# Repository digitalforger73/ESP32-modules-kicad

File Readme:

# ESP32 Community Hardware Project

An open community project for learning ESP32 hardware design with KiCad.

This repository contains a complete ESP32 development board designed in KiCad, intended for makers, students, and engineers who want to learn custom PCB design and build their own ESP32-based hardware.

---

## Features

- ESP32-WROOM-32E
- USB Serial (CH340)
- 3.3V Power Regulator
- Reset / User Buttons
- A status LED / A user LED
- Programming Circuit
- Expansion Headers
- Symbols and Footprints on Components
- Component Replacement Guide

---

## Preview

### PCB

### Schematic

---

## Who is this project for?

- ESP32 beginners
- Electronics hobbyists
- PCB designers
- Students
- Engineers learning KiCad
- Makers who want to build their own ESP32 board

---

## Community Edition

This repository contains the **Community Edition**.

The goal is to provide a minimal but practical ESP32 reference design that anyone can study and build.

---

## Professional Editions

Professional versions are available separately and include additional features such as:

- Buck-Boost Power Supply
- LiPo Battery Charger
- Ultra-Low-Power Design
- Battery Powered Operation
- Additional Sensors
- Production-ready Hardware

---

## Documentation

- Component Replacement Guide
- Assembly Guide
- Hardware Documentation

---

## License

This project is licensed under the **Ippeul Community Hardware License (ICHL)**.

See the LICENSE file for details.

---

## Website

https://www.ippeul.io

---

## Support

If you find this project useful, please consider:

- ⭐ Starring this repository
- Sharing it with other makers
- Visiting https://www.ippeul.io

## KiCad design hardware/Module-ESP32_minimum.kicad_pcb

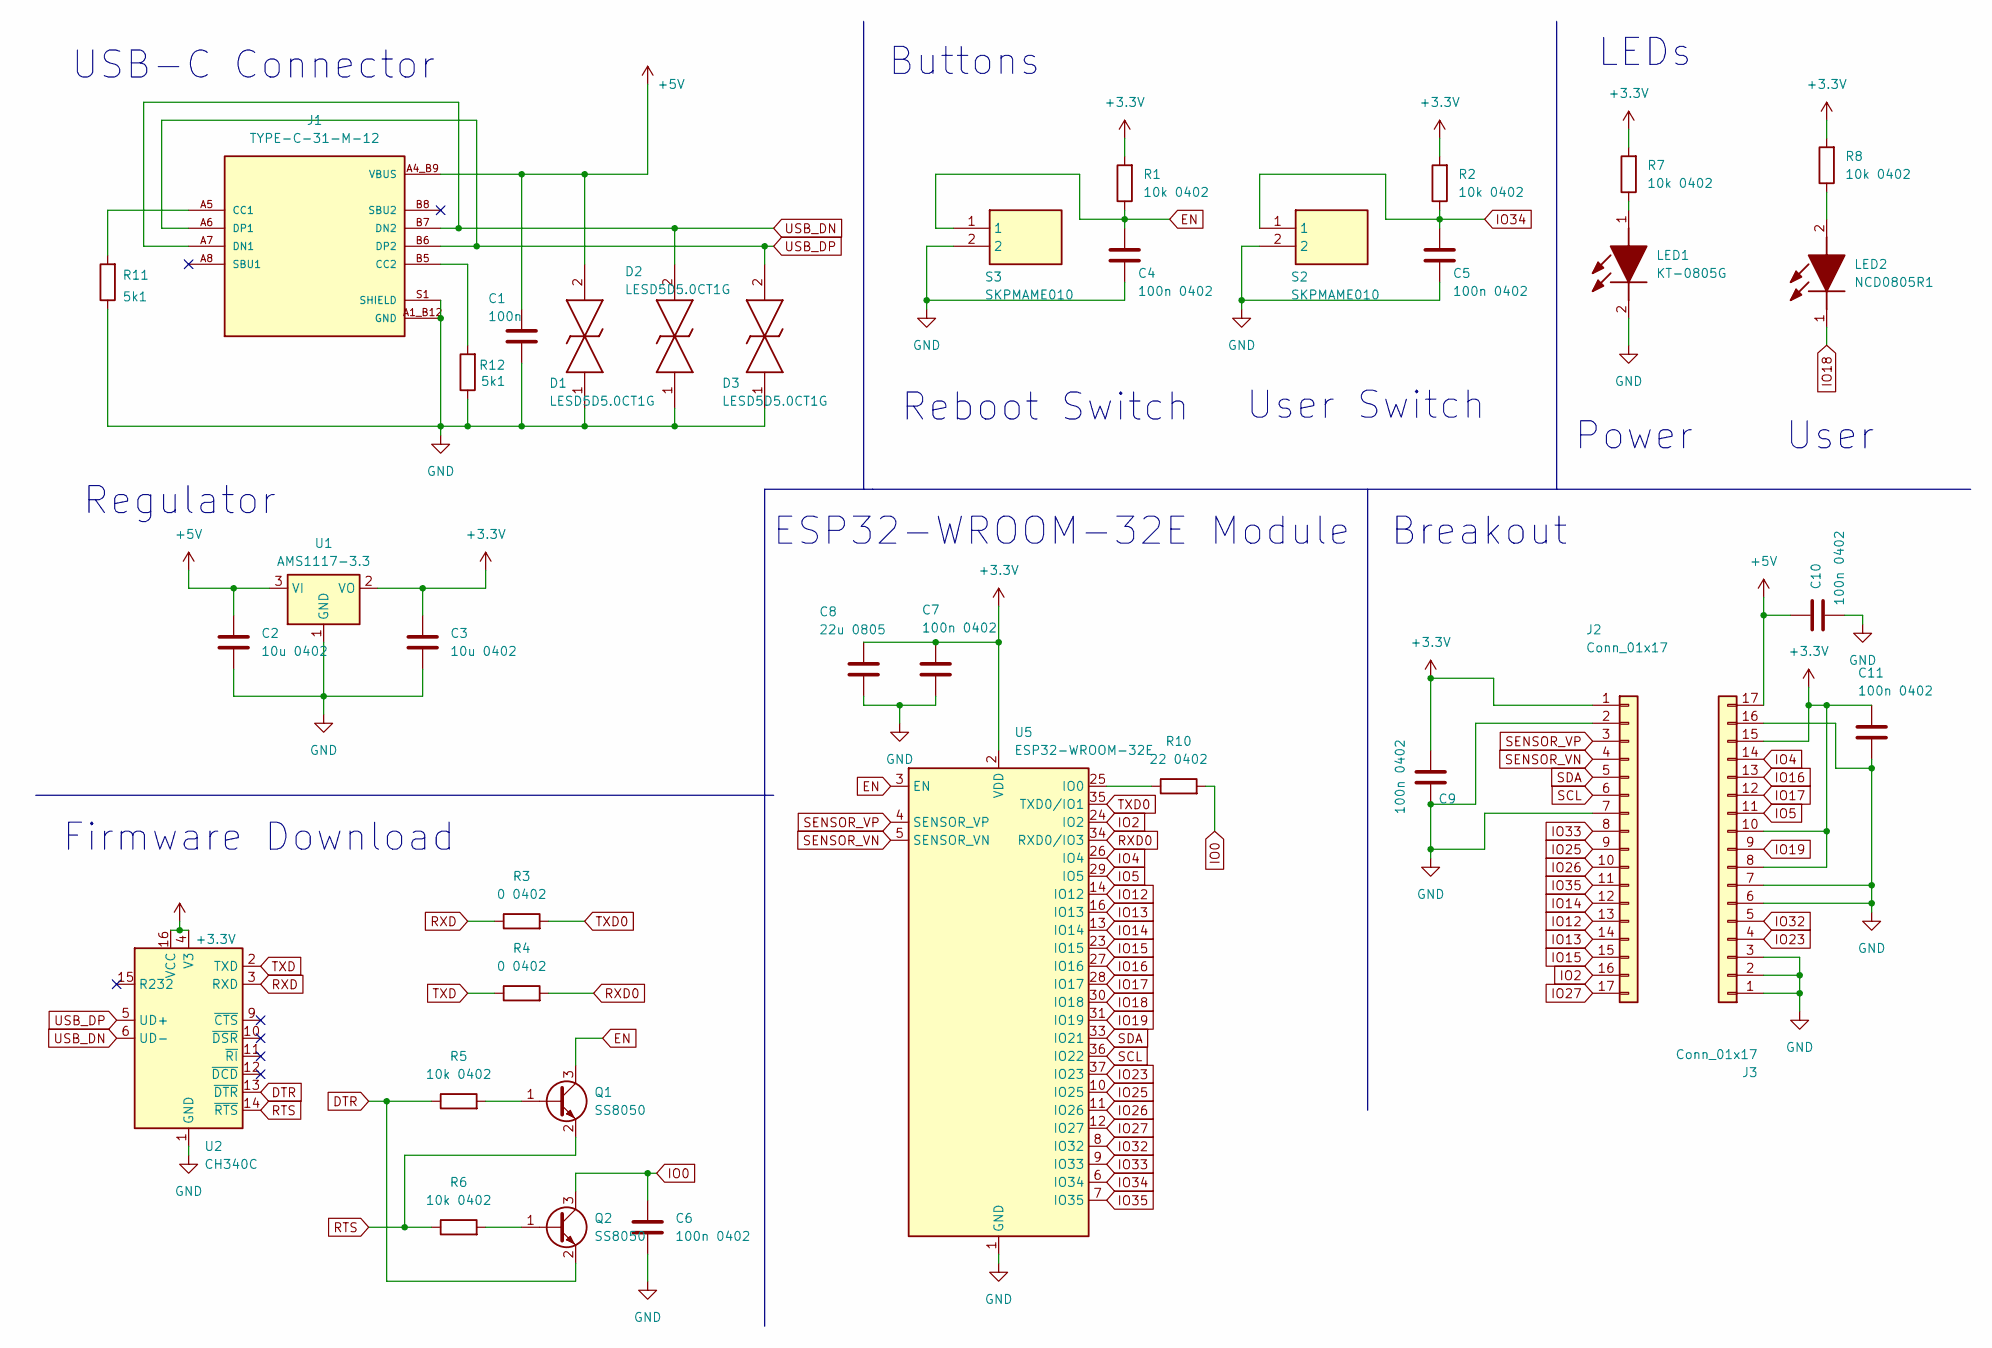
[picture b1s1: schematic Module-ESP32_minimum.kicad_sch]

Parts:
C1: 100n; C_0402_1005Metric
C2, C3: 10u 0402; C_0402_1005Metric
C4, C5, C6, C7, C9, C10, C11: 100n 0402; C_0402_1005Metric
C8: 22u 0805; C_0805_2012Metric
D1, D2, D3: LESD5D5.0CT1G; LESD5D50CT1G; Manufacturer_Part_Number LESD5D5.0CT1G
J1: TYPE-C-31-M-12; HRO_TYPE-C-31-M-12; PARTREV 2020.12.08
J2, J3: Conn_01x17; PinHeader_1x17_P1.27mm_Vertical
LED1: KT-0805G; KT0805G; Manufacturer_Part_Number KT-0805G
LED2: NCD0805R1; LEDC2012X120N; Manufacturer_Part_Number NCD0805R1
Q1, Q2: SS8050; SOT-23
R1, R2, R5, R6, R7, R8: 10k 0402; R_0402_1005Metric
R3, R4: 0 0402; R_0402_1005Metric
R10: 22 0402; R_0402_1005Metric
R11, R12: 5k1; R_0402_1005Metric
S2, S3: SKPMAME010; Manufacturer_Part_Number SKPMAME010; Mouser Part Number 688-SKPMAM
U1: AMS1117-3.3; SOT-223-3_TabPin2
U2: CH340C; STC_SOP-16_3.9x9.9mm_P1.27mm
U5: ESP32-WROOM-32E; ESP32-WROOM-32D

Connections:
+3.3V: C3.1, C7.1, C8.1, C9.1, C11.1, J2.1, J3.8, J3.10, J3.15, R1.2, R2.2, R7.2, R8.2, U1.2 (VO), U2.4 (V3), U2.16 (VCC), U5.2 (VDD)
+5V: C1.1, C2.1, C10.1, D1.2, J1.A4_B9 (VBUS), J1.B4_A9 (VBUS), J3.17, U1.3 (VI)
DTR: Q2.2 (E), R5.1, U2.13 (~DTR)
EN: C4.1, Q1.3 (C), R1.1, S3.1, U5.3 (EN)
GND: C1.2, C2.2, C3.2, C4.2, C5.2, C6.2, C7.2, C8.2, C9.2, C10.2, C11.2, D1.1, D2.1, D3.1, J1.A1_B12 (GND), J1.B1_A12 (GND), J1.S1 (SHIELD), J1.S2 (SHIELD), J1.S3 (SHIELD), J1.S4 (SHIELD), J2.2, J2.7, J3.1, J3.2, J3.3, J3.6, J3.7, J3.16, LED1.2 (K), R11.1, R12.1, S2.2, S3.2, U1.1 (GND), U2.1 (GND), U5.1 (GND), U5.15 (GND), U5.38 (GND), U5.39 (GND)
IO0: C6.1, Q2.3 (C), R10.2
IO2: J2.16, U5.24 (IO2)
IO4: J3.14, U5.26 (IO4)
IO5: J3.11, U5.29 (IO5)
IO12: J2.13, U5.14 (IO12)
IO13: J2.14, U5.16 (IO13)
IO14: J2.12, U5.13 (IO14)
IO15: J2.15, U5.23 (IO15)
IO16: J3.13, U5.27 (IO16)
IO17: J3.12, U5.28 (IO17)
IO18: LED2.1 (K), U5.30 (IO18)
IO19: J3.9, U5.31 (IO19)
IO23: J3.4, U5.37 (IO23)
IO25: J2.9, U5.10 (IO25)
IO26: J2.10, U5.11 (IO26)
IO27: J2.17, U5.12 (IO27)
IO32: J3.5, U5.8 (IO32)
IO33: J2.8, U5.9 (IO33)
IO34: C5.1, R2.1, S2.1, U5.6 (IO34)
IO35: J2.11, U5.7 (IO35)
unnamed: J1.A5 (CC1), R11.2
unnamed: J1.B5 (CC2), R12.2
unnamed: LED1.1 (A), R7.1
unnamed: LED2.2 (A), R8.1
unnamed: Q1.1 (B), R5.2
unnamed: Q2.1 (B), R6.2
unnamed: R10.1, U5.25 (IO0)
RTS: Q1.2 (E), R6.1, U2.14 (~RTS)
RXD: R3.1, U2.3 (RXD)
RXD0: R4.2, U5.34 (RXD0/IO3)
SCL: J2.6, U5.36 (IO22)
SDA: J2.5, U5.33 (IO21)
SENSOR_VN: J2.4, U5.5 (SENSOR_VN)
SENSOR_VP: J2.3, U5.4 (SENSOR_VP)
TXD: R4.1, U2.2 (TXD)
TXD0: R3.2, U5.35 (TXD0/IO1)
USB_DN: D2.2, J1.A7 (DN1), J1.B7 (DN2), U2.6 (UD-)
USB_DP: D3.2, J1.A6 (DP1), J1.B6 (DP2), U2.5 (UD+)

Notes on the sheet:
USB-C Connector
Power
User
Regulator
ESP32-WROOM-32E Module
User Switch
Buttons
Breakout
Reboot Switch
Firmware Download
LEDs

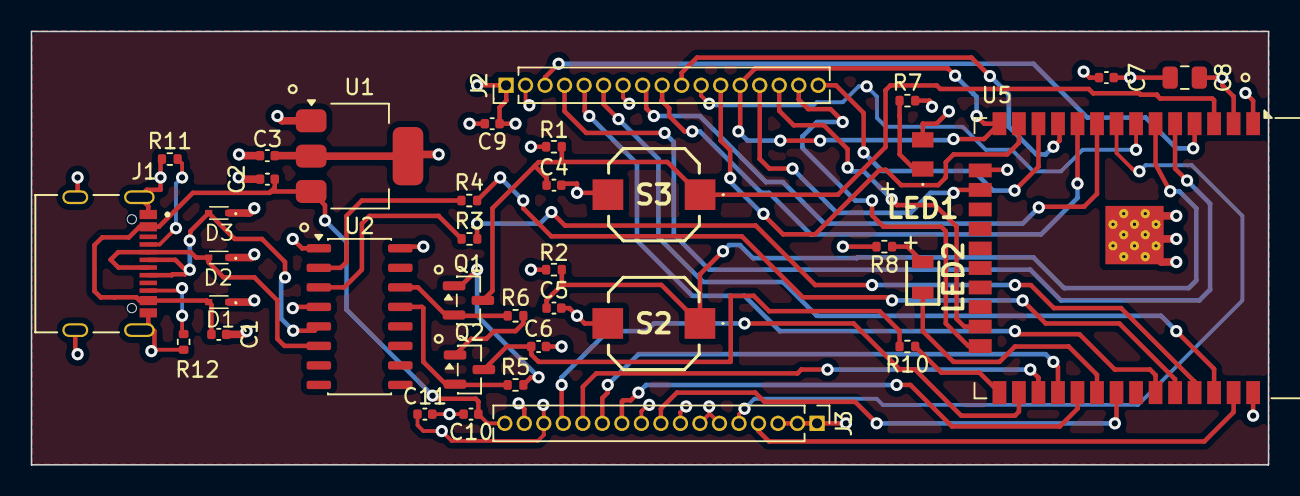
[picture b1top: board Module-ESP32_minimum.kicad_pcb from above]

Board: 4 copper layers, 80.5 x 28.2 mm, 37 parts (0 on the bottom side), 43 nets.
